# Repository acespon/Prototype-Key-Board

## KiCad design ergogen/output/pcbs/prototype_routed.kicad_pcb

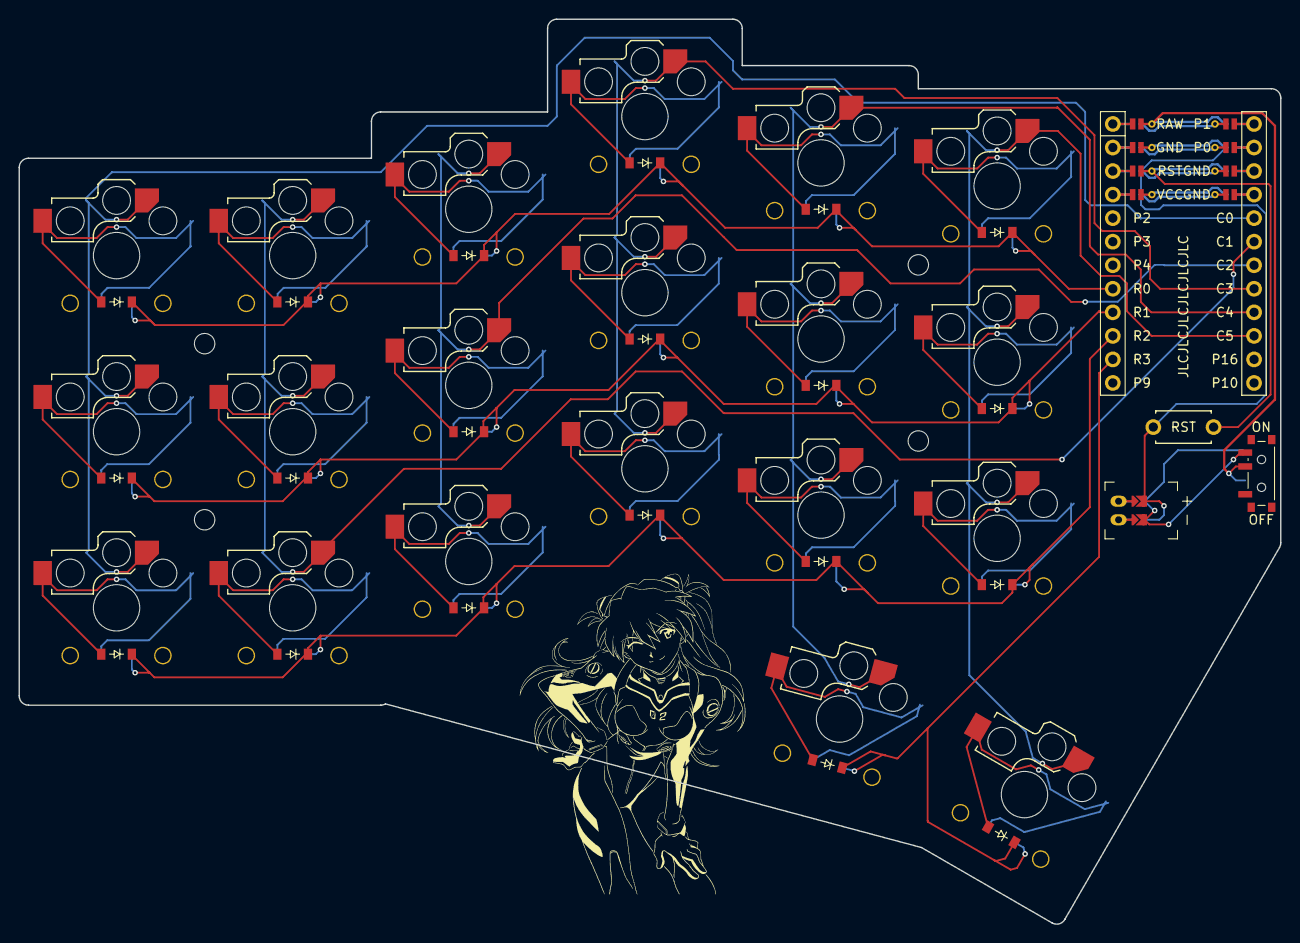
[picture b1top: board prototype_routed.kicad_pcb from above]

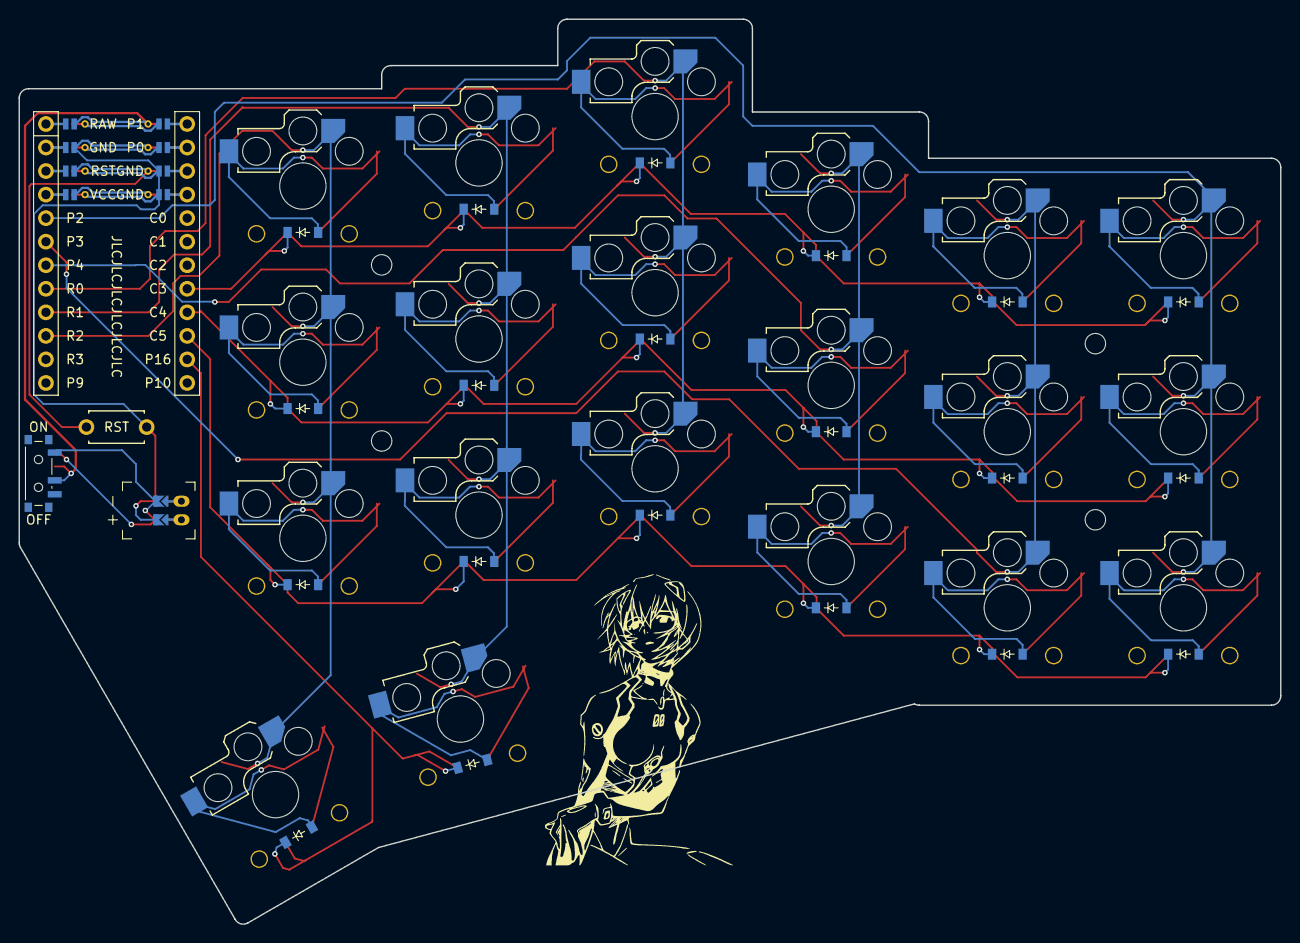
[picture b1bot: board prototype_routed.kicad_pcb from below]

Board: 2 copper layers, 136.1 x 97.6 mm, 51 parts (21 on the bottom side), 40 nets.

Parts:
Asuka: LOGO
D1, D2, D3, D4, D5, D6, D7, D8, D9, D10, D11, D12, D13, D14, D15, D16, D17, D18, D19, D20: diode_tht_sod123
JST1: battery_connector_jst_ph_2
LOGO1: utility_ergogen_logo
MCU1: mcu_nice_nano
MH1, MH2, MH3, MH4: mounting_hole_npth
PWR1: power_switch_smd_side
RST1: reset_switch_tht_top
Rei: LOGO
S1, S2, S3, S4, S5, S6, S7, S8, S9, S10, S11, S12, S13, S14, S15, S16, S17, S18, S19, S20: switch_choc_v1_v2

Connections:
BAT_P: JST1.1, PWR1.1, PWR1.3
C0: MCU1.5, S1.1, S2.1, S3.1
C1: MCU1.6, S4.1, S5.1, S6.1
C2: MCU1.7, S7.1, S8.1, S9.1
C3: MCU1.8, S10.1, S11.1, S12.1
C4: MCU1.9, S13.1, S14.1, S15.1, S19.1
C5: MCU1.10, S16.1, S17.1, S18.1, S20.1
GND: JST1.2, MCU1.103, MCU1.104, MCU1.123, RST1.2
JST1_1: JST1.11, JST1.21, JST1.31
JST1_2: JST1.12, JST1.22, JST1.32
MCU1_1: MCU1.1, MCU1.24
MCU1_2: MCU1.2, MCU1.23
MCU1_3: MCU1.3, MCU1.22
MCU1_4: MCU1.4, MCU1.21
R0: D3.1, D6.1, D9.1, D12.1, D15.1, D18.1, MCU1.17
R1: D2.1, D5.1, D8.1, D11.1, D14.1, D17.1, MCU1.16
R2: D1.1, D4.1, D7.1, D10.1, D13.1, D16.1, MCU1.15
R3: D19.1, D20.1, MCU1.14
RAW: MCU1.124, PWR1.2
RST: MCU1.122, RST1.1
index_bottom: D13.2, S13.2
index_home: D14.2, S14.2
index_top: D15.2, S15.2
indexfar_bottom: D16.2, S16.2
indexfar_home: D17.2, S17.2
indexfar_top: D18.2, S18.2
layer_cluster: D19.2, S19.2
middle_bottom: D10.2, S10.2
middle_home: D11.2, S11.2
middle_top: D12.2, S12.2
outer_bottom: D1.2, S1.2
outer_home: D2.2, S2.2
outer_top: D3.2, S3.2
pinky_bottom: D4.2, S4.2
pinky_home: D5.2, S5.2
pinky_top: D6.2, S6.2
ring_bottom: D7.2, S7.2
ring_home: D8.2, S8.2
ring_top: D9.2, S9.2
space_cluster: D20.2, S20.2

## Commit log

2024-11-24 feat: Initial config file
2024-11-24 feat: add matrix
2024-11-27 feat: Change diode layout, edit outlines
2024-11-27 feat: refine layout, add battery connector
2024-11-27 feat: add reset button, on/off switch
2024-12-02 feat: ceoloide suggestions
2024-12-02 feat: reformat, spacing
2024-12-02 feat: mounting holes
2024-12-02 feat: updated footprints, suggestions
2024-12-04 feat: routing, silkscreen
2024-12-04 feat: Routed PCB screenshot
2024-12-04 feat: fix Screenshot
2024-12-26 feat: updated PCB
